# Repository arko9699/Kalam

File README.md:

# Kalam
 A 40% keyboard PCB project

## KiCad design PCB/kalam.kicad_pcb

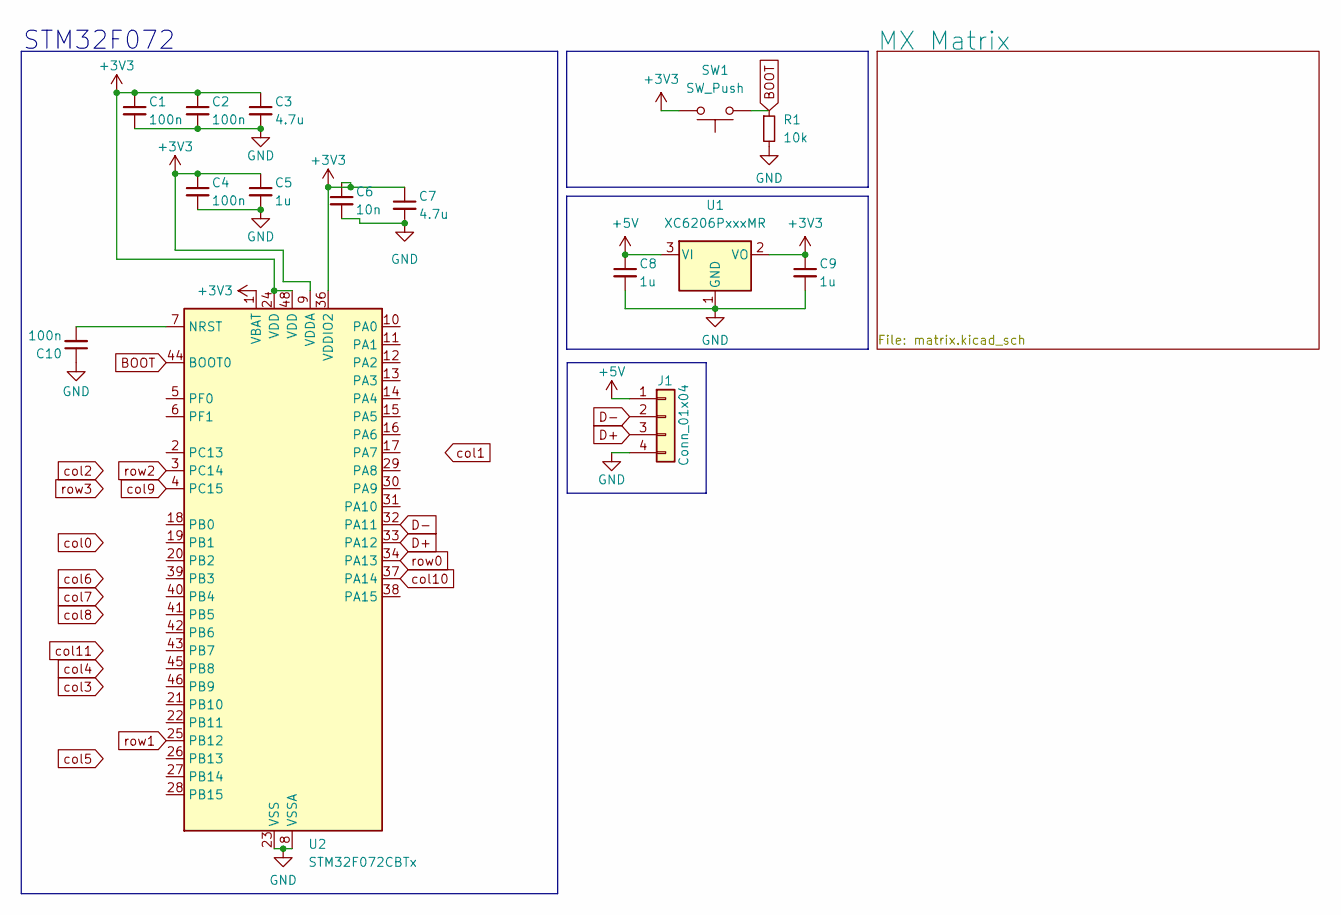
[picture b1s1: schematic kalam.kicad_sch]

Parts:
C1, C2, C4, C10: 100n; C_0402_1005Metric
C3, C7: 4.7u; C_0603_1608Metric
C5, C8, C9: 1u; C_0603_1608Metric
C6: 10n; C_0402_1005Metric
J1: Conn_01x04; JST_SH_SM04B-SRSS-TB_1x04-1MP_P1.00mm_Horizontal
R1: 10k; R_0603_1608Metric
SW1: SW_Push; SW_Push_1P1T_XKB_TS-1187A
U1: XC6206PxxxMR; SOT-23-3
U2: STM32F072CBTx; LQFP-48_7x7mm_P0.5mm

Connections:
+3V3: C1.1, C2.1, C3.1, C4.1, C5.1, C6.1, C7.1, C9.1, SW1.2, U1.2 (VO), U2.1 (VBAT), U2.9 (VDDA), U2.24 (VDD), U2.36 (VDDIO2), U2.48 (VDD)
+5V: C8.1, J1.1, U1.3 (VI)
BOOT: R1.1, SW1.1, U2.44 (BOOT0)
D+: J1.3, U2.33 (PA12)
D-: J1.2, U2.32 (PA11)
GND: C1.2, C2.2, C3.2, C4.2, C5.2, C6.2, C7.2, C8.2, C9.2, C10.1, J1.4, R1.2, U1.1 (GND), U2.8 (VSSA), U2.23 (VSS), U2.35 (VSS), U2.47 (VSS)
unnamed: C10.2, U2.7 (NRST)
col0: U2.21 (PB10); also elsewhere on the board
col1: U2.19 (PB1); also elsewhere on the board
col2: U2.17 (PA7); also elsewhere on the board
col3: U2.43 (PB7); also elsewhere on the board
col4: U2.42 (PB6); also elsewhere on the board
col5: U2.15 (PA5); also elsewhere on the board
col6: U2.41 (PB5); also elsewhere on the board
col7: U2.40 (PB4); also elsewhere on the board
col8: U2.13 (PA3); also elsewhere on the board
col9: U2.4 (PC15); also elsewhere on the board
col10: U2.37 (PA14); also elsewhere on the board
col11: U2.38 (PA15); also elsewhere on the board
row0: U2.34 (PA13); also elsewhere on the board
row1: U2.25 (PB12); also elsewhere on the board
row2: U2.3 (PC14); also elsewhere on the board
row3: U2.39 (PB3); also elsewhere on the board

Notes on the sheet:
STM32F072

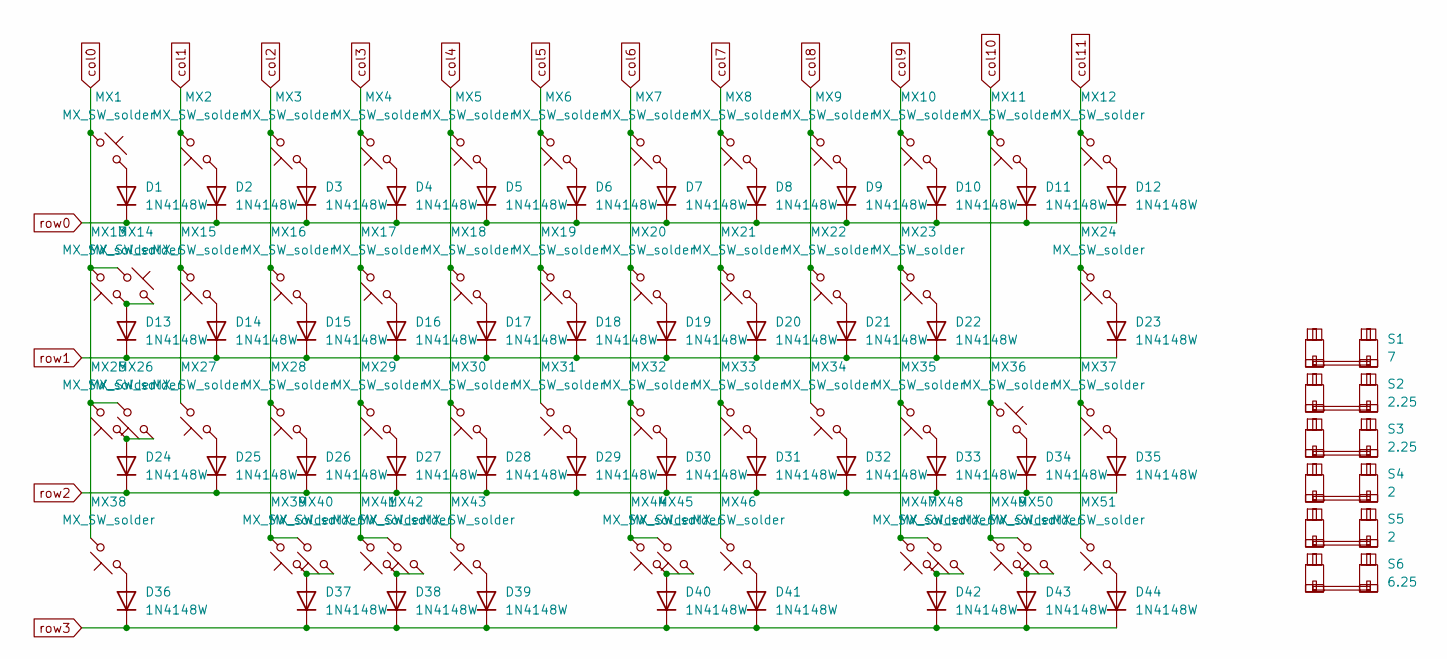
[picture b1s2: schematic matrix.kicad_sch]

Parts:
D1, D2, D3, D4, D5, D6, D7, D8, D9, D10, D11, D12, D13, D14, D15, D16, D17, D18, D19, D20, D21, D22, D23, D24, D25, D26, D27, D28, D29, D30, D31, D32, D33, D34, D35, D36, D37, D38, D39, D40, D41, D42, D43, D44: 1N4148W; D_SOD-123
MX1, MX12: MX_SW_solder; SW_MX_1.5u
MX2, MX3, MX4, MX5, MX6, MX7, MX8, MX9, MX10, MX11, MX15, MX16, MX17, MX18, MX19, MX20, MX21, MX22, MX23, MX24, MX25, MX27, MX28, MX29, MX30, MX31, MX32, MX33, MX34, MX35, MX37, MX40, MX42, MX43, MX44, MX45, MX46, MX48, MX50: MX_SW_solder; SW_MX_1u
MX13, MX36: MX_SW_solder; SW_MX_1.75u
MX14: MX_SW_solder; SW_MX_1.75u_STP_1.25
MX26, MX38, MX39, MX41, MX47, MX49, MX51: MX_SW_solder; SW_MX_1.25u
S1: 7; STAB_MX_P_7u
S2, S3: 2.25; STAB_MX_P_2.25u
S4, S5: 2; STAB_MX_P_2u
S6: 6.25; STAB_MX_P_6.25u

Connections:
unnamed: D1.2 (A), MX1.2
unnamed: D2.2 (A), MX2.1
unnamed: D3.2 (A), MX3.1
unnamed: D4.2 (A), MX4.1
unnamed: D5.2 (A), MX5.1
unnamed: D6.2 (A), MX6.1
unnamed: D7.2 (A), MX7.1
unnamed: D8.2 (A), MX8.1
unnamed: D9.2 (A), MX9.1
unnamed: D10.2 (A), MX10.1
unnamed: D11.2 (A), MX11.1
unnamed: D12.2 (A), MX12.1
unnamed: D13.2 (A), MX13.1, MX14.2
unnamed: D14.2 (A), MX15.1
unnamed: D15.2 (A), MX16.1
unnamed: D16.2 (A), MX17.1
unnamed: D17.2 (A), MX18.1
unnamed: D18.2 (A), MX19.1
unnamed: D19.2 (A), MX20.1
unnamed: D20.2 (A), MX21.1
unnamed: D21.2 (A), MX22.1
unnamed: D22.2 (A), MX23.1
unnamed: D23.2 (A), MX24.1
unnamed: D24.2 (A), MX25.1, MX26.1
unnamed: D25.2 (A), MX27.1
unnamed: D26.2 (A), MX28.1
unnamed: D27.2 (A), MX29.1
unnamed: D28.2 (A), MX30.1
unnamed: D29.2 (A), MX31.1
unnamed: D30.2 (A), MX32.1
unnamed: D31.2 (A), MX33.1
unnamed: D32.2 (A), MX34.1
unnamed: D33.2 (A), MX35.1
unnamed: D34.2 (A), MX36.2
unnamed: D35.2 (A), MX37.1
unnamed: D36.2 (A), MX38.1
unnamed: D37.2 (A), MX39.1, MX40.1
unnamed: D38.2 (A), MX41.1, MX42.1
unnamed: D39.2 (A), MX43.1
unnamed: D40.2 (A), MX44.1, MX45.1
unnamed: D41.2 (A), MX46.1
unnamed: D42.2 (A), MX47.1, MX48.1
unnamed: D43.2 (A), MX49.1, MX50.1
unnamed: D44.2 (A), MX51.1
col0: MX1.1, MX13.2, MX14.1, MX25.2, MX26.2, MX38.2; also elsewhere on the board
col1: MX2.2, MX15.2, MX27.2; also elsewhere on the board
col2: MX3.2, MX16.2, MX28.2, MX39.2, MX40.2; also elsewhere on the board
col3: MX4.2, MX17.2, MX29.2, MX41.2, MX42.2; also elsewhere on the board
col4: MX5.2, MX18.2, MX30.2, MX43.2; also elsewhere on the board
col5: MX6.2, MX19.2, MX31.2; also elsewhere on the board
col6: MX7.2, MX20.2, MX32.2, MX44.2, MX45.2; also elsewhere on the board
col7: MX8.2, MX21.2, MX33.2, MX46.2; also elsewhere on the board
col8: MX9.2, MX22.2, MX34.2; also elsewhere on the board
col9: MX10.2, MX23.2, MX35.2, MX47.2, MX48.2; also elsewhere on the board
col10: MX11.2, MX36.1, MX49.2, MX50.2; also elsewhere on the board
col11: MX12.2, MX24.2, MX37.2, MX51.2; also elsewhere on the board
row0: D1.1 (K), D2.1 (K), D3.1 (K), D4.1 (K), D5.1 (K), D6.1 (K), D7.1 (K), D8.1 (K), D9.1 (K), D10.1 (K), D11.1 (K), D12.1 (K); also elsewhere on the board
row1: D13.1 (K), D14.1 (K), D15.1 (K), D16.1 (K), D17.1 (K), D18.1 (K), D19.1 (K), D20.1 (K), D21.1 (K), D22.1 (K), D23.1 (K); also elsewhere on the board
row2: D24.1 (K), D25.1 (K), D26.1 (K), D27.1 (K), D28.1 (K), D29.1 (K), D30.1 (K), D31.1 (K), D32.1 (K), D33.1 (K), D34.1 (K), D35.1 (K); also elsewhere on the board
row3: D36.1 (K), D37.1 (K), D38.1 (K), D39.1 (K), D40.1 (K), D41.1 (K), D42.1 (K), D43.1 (K), D44.1 (K); also elsewhere on the board

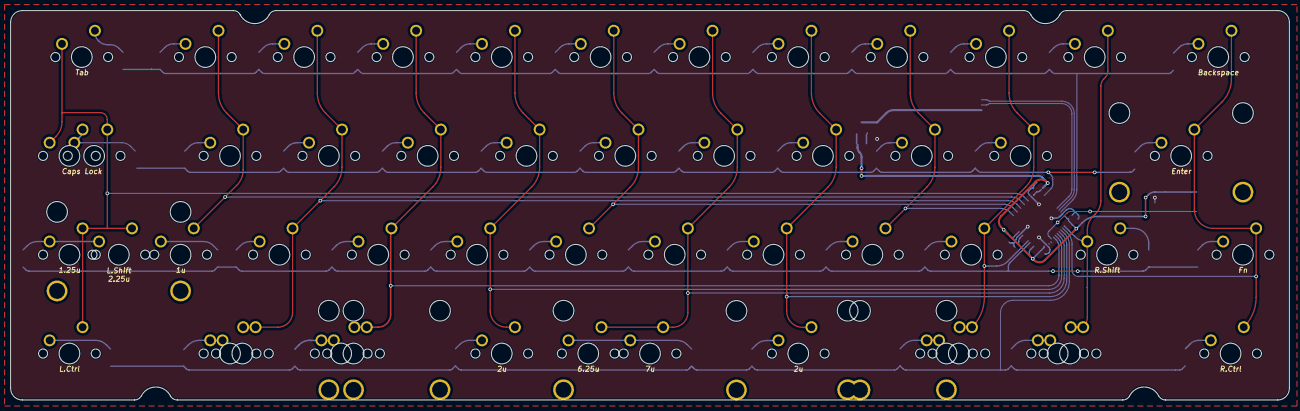
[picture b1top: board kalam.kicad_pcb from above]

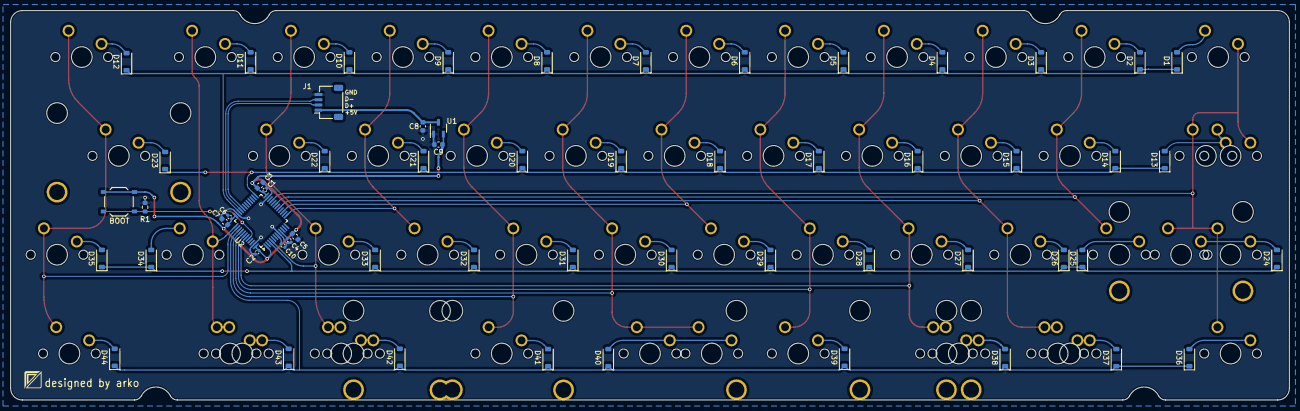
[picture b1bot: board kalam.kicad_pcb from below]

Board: 2 copper layers, 246.5 x 75.1 mm, 116 parts (59 on the bottom side), 67 nets.

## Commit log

2024-08-11 Added PCB files
    Files for the PCB
2024-08-11 Rename from working
2024-08-12 More files added
    Gerber files for PCB along with BOM and CPL files. Also added picture of supported layouts
2024-08-31 PCB Fab v1
2024-10-02 back to the drawing board
2024-10-03 beeg overhaul and new layout image
2024-10-03 deleted old files
